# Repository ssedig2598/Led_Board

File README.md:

# Led_Board
These are the files for the new iteration of LED boards with yellow and orange LEDS

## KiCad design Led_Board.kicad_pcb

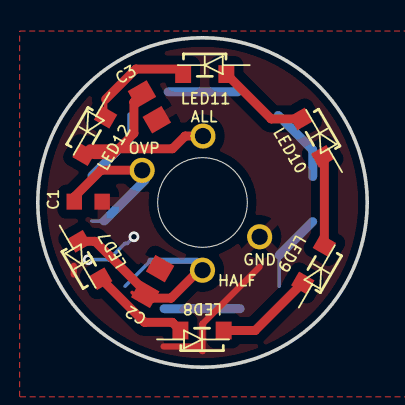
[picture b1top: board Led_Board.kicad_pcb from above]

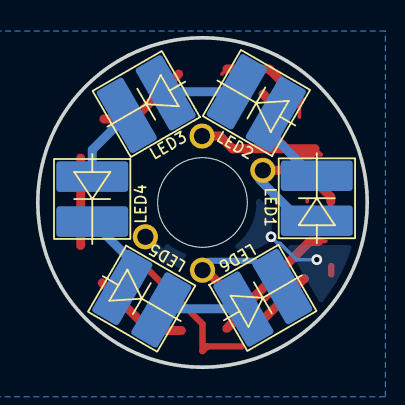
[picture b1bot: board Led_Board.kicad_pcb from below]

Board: 2 copper layers, 18.3 x 18.3 mm, 19 parts (6 on the bottom side), 14 nets.

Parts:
ALL: hole
C1: GRT188R61H105KE13D; CAP_GRT188R61H105KE13D_MUR
C2, C3: CC0805KRX7R9BB104; CC0805N_YAG
GND: hole
HALF: hole
LED1, LED2, LED3, LED4, LED5, LED6: AA4040SYCKT_J3-AMT
LED7, LED9, LED11: APA2107SECK_J4-PRV
LED8, LED10, LED12: APA2107SECK/J4-PRV; APA2107SECK_J4-PRV
OVP: hole

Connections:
GND: C1.2, C2.2, C3.2, GND.1
unnamed: C1.1, LED1.2, OVP.1
unnamed: C2.1, HALF.1, LED6.1, LED7.2
unnamed: ALL.1, C3.1, LED12.1
unnamed: LED1.1, LED2.2
unnamed: LED2.1, LED3.2
unnamed: LED3.1, LED4.2
unnamed: LED4.1, LED5.2
unnamed: LED5.1, LED6.2
unnamed: LED7.1, LED8.2
unnamed: LED8.1, LED9.2
unnamed: LED10.1, LED11.2
unnamed: LED9.1, LED10.2
unnamed: LED11.1, LED12.2

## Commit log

2024-03-10 New files added to the project
2024-03-10 Reorg
2024-03-31 newest updates
